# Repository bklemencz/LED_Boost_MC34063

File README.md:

# LED_Boost_MC34063
MC34063 based 24V/32V 300mA LED Boost mode driver with Dimming Input

It can drive 10 series 1W LEDs with 300mA. 
300mA is the maximum for the CD75 inductor.
Dimming input is 5V positive logic (Logic 1 - LED On).

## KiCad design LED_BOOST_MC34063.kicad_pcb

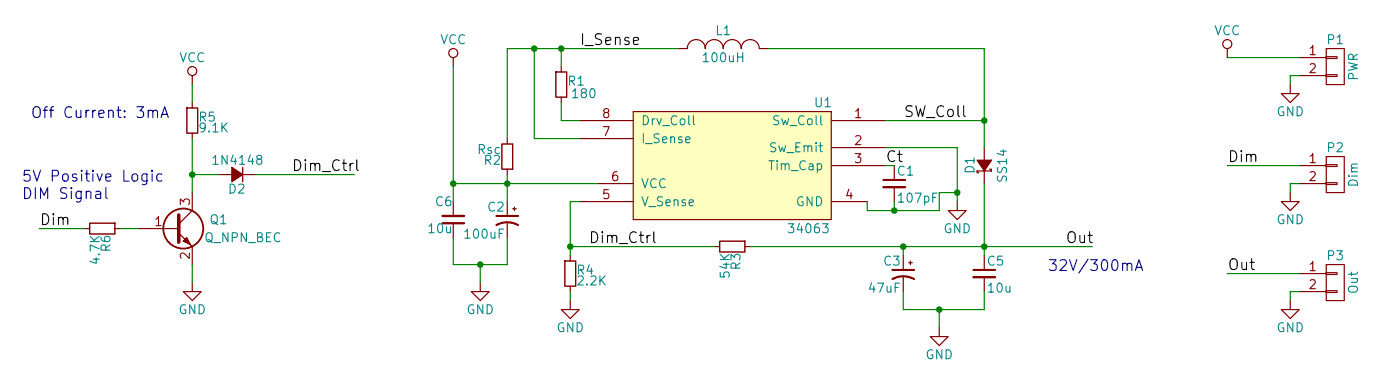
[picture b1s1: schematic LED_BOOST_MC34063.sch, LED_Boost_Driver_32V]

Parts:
C1: 107pF; C_0805
C2: 100uF; CP_Elec_6.3x7.7
C3: 47uF; CP_Elec_6.3x7.7
C5, C6: 10u; C_1206
D1: SS14; D_SMA
D2: 1N4148; D_0805
L1: 100uH; IND_SMD_CD75
P1: PWR; Pin_Header_Straight_1x02_Pitch2.54mm
P2: Dim; Pin_Header_Straight_1x02_Pitch2.54mm
P3: Out; Pin_Header_Straight_1x02_Pitch2.54mm
Q1: Q_NPN_BEC; SOT-23
R1: 180; R_0805
R2: Rsc; R_1206
R3: 54K; R_0805
R4: 2.2K; R_0805
R5: 9.1K; R_0805
R6: 4.7K; R_0805
U1: 34063; SOIC-8_3.9x4.9mm_Pitch1.27mm

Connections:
/Ct: C1.1, U1.3 (Tim_Cap)
/Dim: P2.1, R6.2
/Dim_C: D2.2 (A), Q1.3 (C), R5.2
/Dim_Ctrl: D2.1 (K), R3.2, R4.1, U1.5 (V_Sense)
/Drv_Coll: R1.2, U1.8 (Drv_Coll)
/I_Sense: L1.1, R1.1, R2.2, U1.7 (I_Sense)
/Out: C3.1, C5.1, D1.1 (K), P3.1, R3.1
/SW_Coll: D1.2 (A), L1.2, U1.1 (Sw_Coll)
GND: C1.2, C2.2, C3.2, C5.2, C6.1, P1.2, P2.2, P3.2, Q1.2 (E), R4.2, U1.2 (Sw_Emit), U1.4 (GND)
unnamed: Q1.1 (B), R6.1
VCC: C2.1, C6.2, P1.1, R2.1, R5.1, U1.6 (VCC)

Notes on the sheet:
32V/300mA
Off Current: 3mA
5V Positive Logic DIM Signal

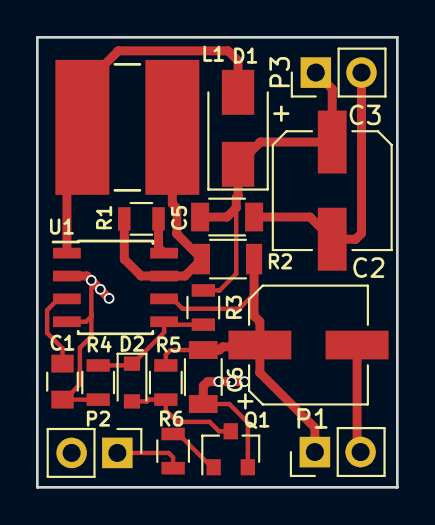
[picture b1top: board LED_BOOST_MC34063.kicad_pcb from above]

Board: 2 copper layers, 20.0 x 25.0 mm, 19 parts (0 on the bottom side), 11 nets.

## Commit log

2017-11-13 :octocat: Added .gitattributes & .gitignore files
2017-11-13 Initial
2017-11-13 Calculator Spreadsheet Added
2017-12-04 PCB_Update
